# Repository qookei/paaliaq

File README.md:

# Paaliaq

Paaliaq is a WDC W65C816-based single board computer and the
accompanying software, with support for e.g. modern memory management
features, and kernel/user priviledge separation.

The project is currently in early stages of development, with most of
the current work focusing on the chipset implemntation. Proper
documentation TBD.

## Specifications

Using the QMTECH XC7A100T Wukong board with the following
specifications as the base FPGA board:

 - Xilinx Artix-7 100T FPGA
 - 32MiB of SDR SDRAM
 - 8MiB SPI flash (holding the bitstream, with free space after it)
 - SD card slot
 - Ethernet port with GMII PHY
 - Some LEDs and buttons
 - 4 PMODs, 40 pin header exposing 34 FPGA I/Os (see below for usage).

Attached to the FPGA board's 40 pin header is an adapter board holding
a DIP40 variant of the 65C816 CPU, currently running at approximately
4 MHz.

## How?

Supporting the features mentioned above is made possible due to the
inclusion of the `ABORTB` signal on the 65C816 CPU, which allows the
currently executing instruction to be aborted, preventing register
changes and memory reads/writes, and allowing the instruction to
potentially be retried after returning from the handler.

To facilitate this, the FPGA contains not only the memory controller
and various peripherals, but also a page-based memory management unit,
which performs address translation and permission checks, signaling
errors to the CPU via the aforementioned abort signal.

## Directory structure and building

Each of the following subdirectories has instructions on how to build
it's contents:

 - `rtl` - The source code for the FPGA implementation of the chipset.
 - `toolchain` - The source code for the toolchain (assembler, etc).
 - `fw` - The source code for the firmware (embedded in BRAM).
 - `kern` - The source code for the kernel (loaded over serial).

## License

This project is licensed under the GNU General Public License, either
version 3, or (at your opinion) any later version.

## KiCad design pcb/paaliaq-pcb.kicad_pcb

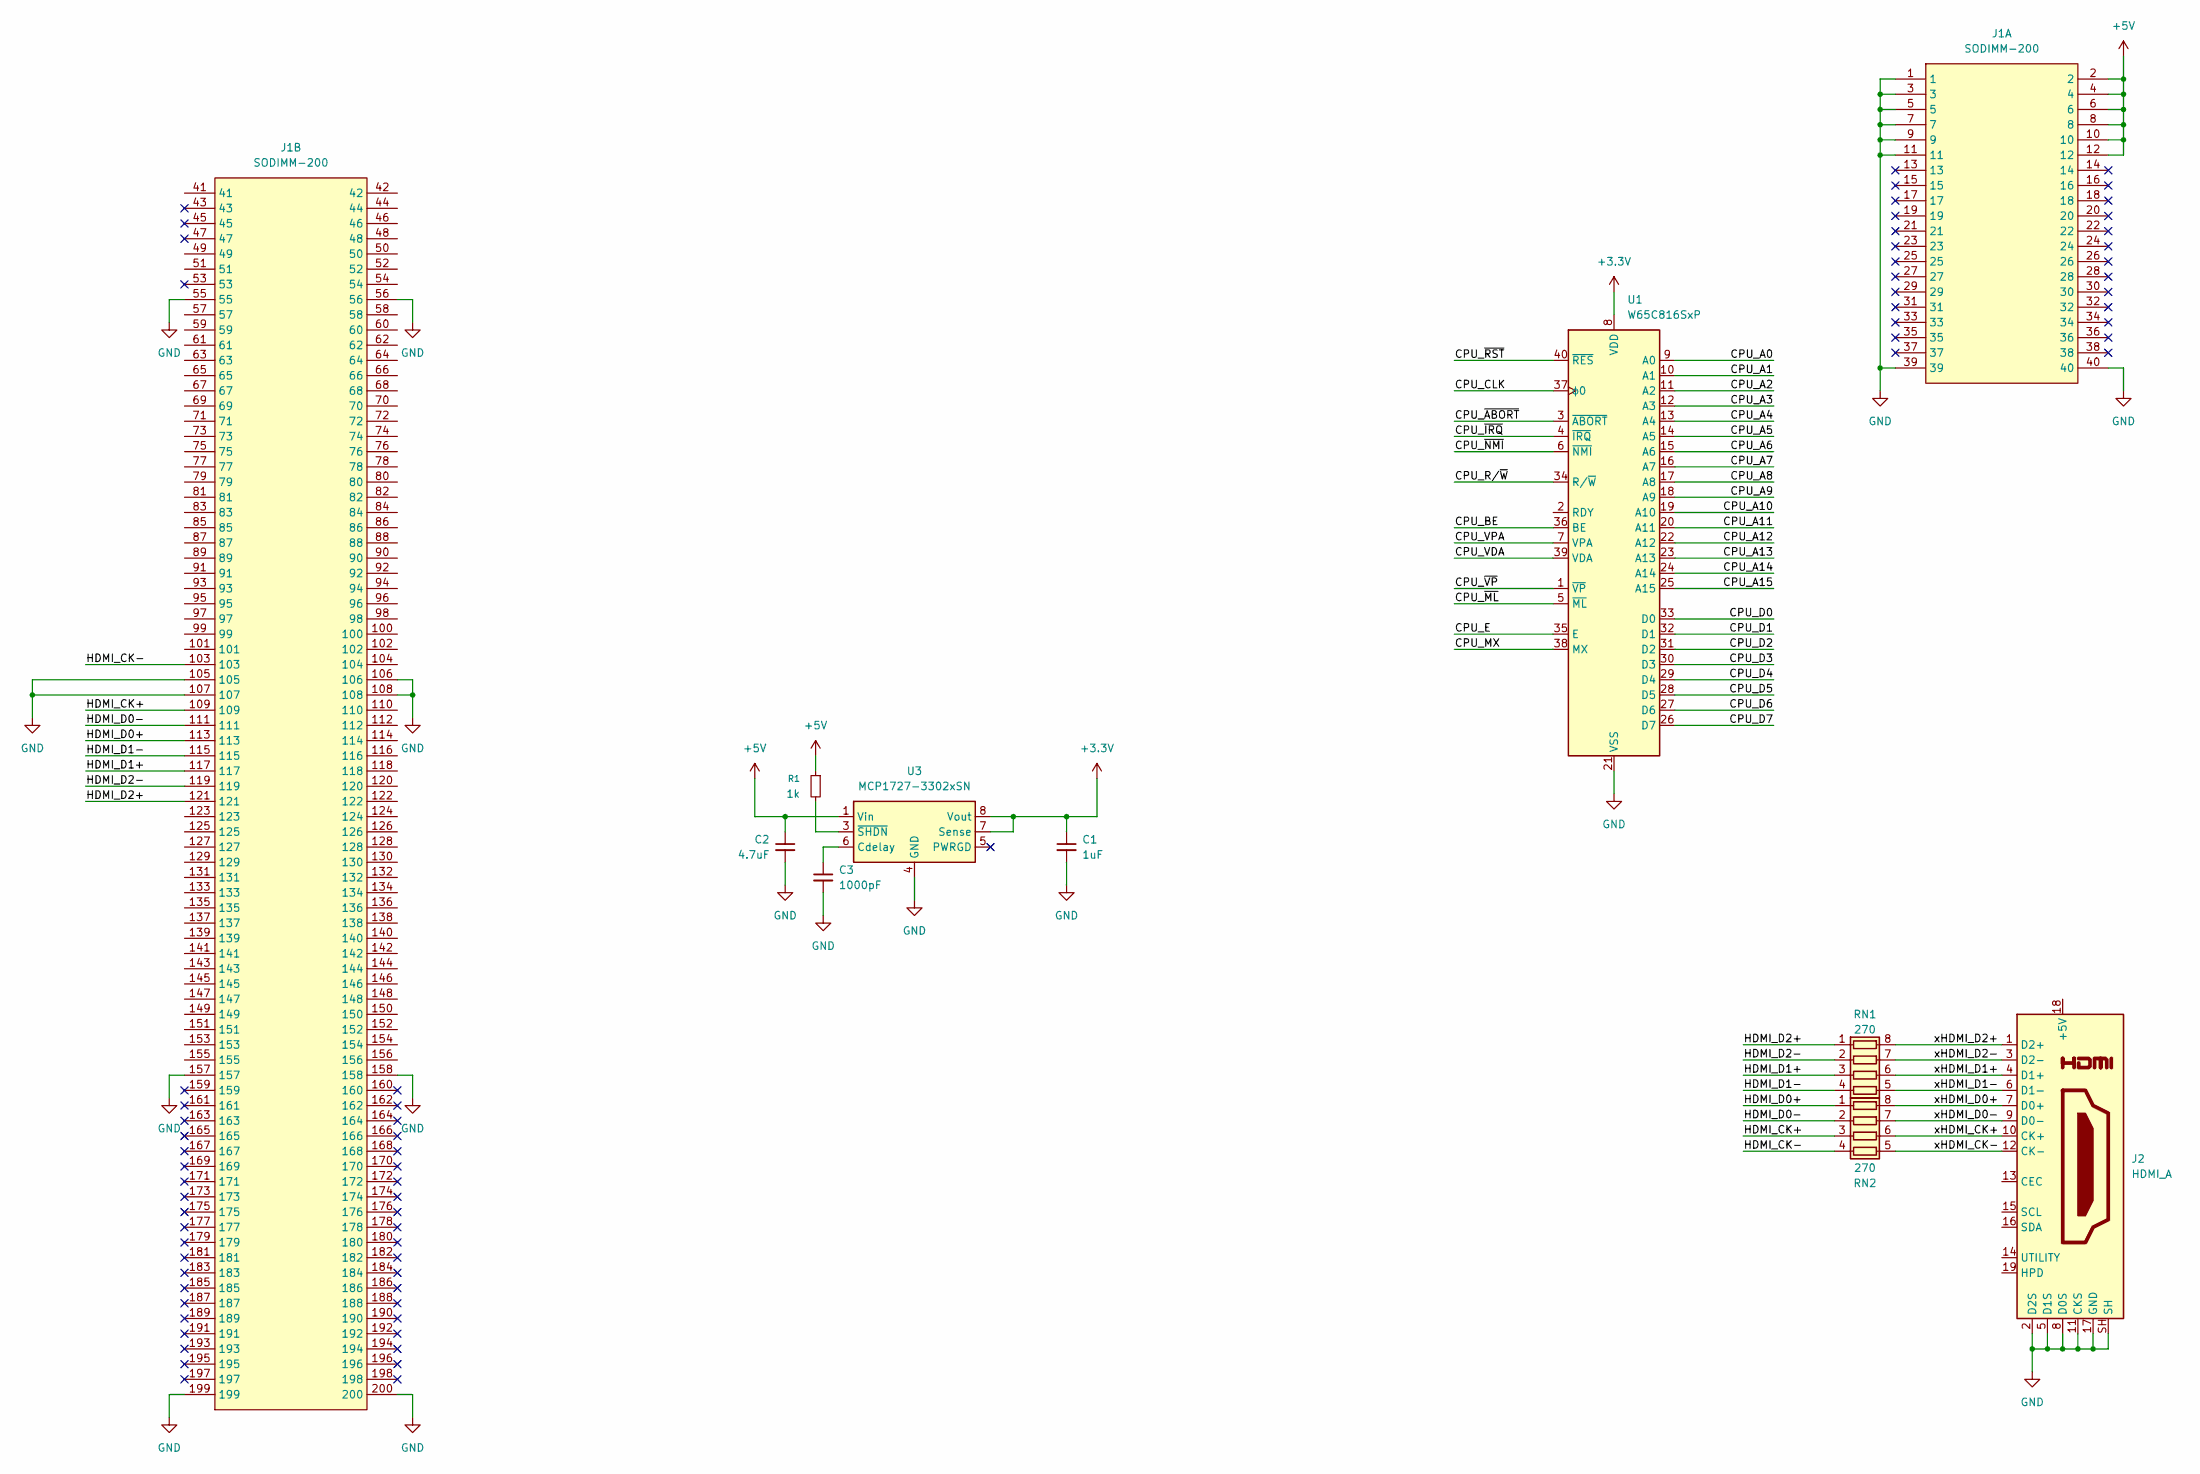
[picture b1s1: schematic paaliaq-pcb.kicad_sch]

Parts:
C1: 1uF; C_0805_2012Metric_Pad1.18x1.45mm_HandSolder
C2: 4.7uF; C_0805_2012Metric_Pad1.18x1.45mm_HandSolder
C3: 1000pF; C_0805_2012Metric_Pad1.18x1.45mm_HandSolder
J1: SODIMM-200; TE_1473005-1_2x100_P0.6mm_Horizontal
J2: HDMI_A; HDMI_A_Amphenol_10029449-x01xLF_Horizontal
R1: 1k; R_0805_2012Metric_Pad1.20x1.40mm_HandSolder
RN1, RN2: 270; R_Array_Convex_4x1206
U1: W65C816SxP; DIP-40_W15.24mm_Socket
U3: MCP1727-3302xSN; SOIC-8_3.9x4.9mm_P1.27mm

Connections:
+3.3V: C1.1, U1.8 (VDD), U3.7 (Sense), U3.8 (Vout)
+5V: C2.1, J1.2, J1.4, J1.6, J1.8, J1.10, J1.12, R1.1, U3.1 (Vin), U3.2 (Vin)
/CPU_A0: U1.9 (A0)
/CPU_A1: U1.10 (A1)
/CPU_A2: U1.11 (A2)
/CPU_A3: U1.12 (A3)
/CPU_A4: U1.13 (A4)
/CPU_A5: U1.14 (A5)
/CPU_A6: U1.15 (A6)
/CPU_A7: U1.16 (A7)
/CPU_A8: U1.17 (A8)
/CPU_A9: U1.18 (A9)
/CPU_A10: U1.19 (A10)
/CPU_A11: U1.20 (A11)
/CPU_A12: U1.22 (A12)
/CPU_A13: U1.23 (A13)
/CPU_A14: U1.24 (A14)
/CPU_A15: U1.25 (A15)
/CPU_BE: U1.36 (BE)
/CPU_CLK: U1.37 (ϕ0)
/CPU_D0: U1.33 (D0)
/CPU_D1: U1.32 (D1)
/CPU_D2: U1.31 (D2)
/CPU_D3: U1.30 (D3)
/CPU_D4: U1.29 (D4)
/CPU_D5: U1.28 (D5)
/CPU_D6: U1.27 (D6)
/CPU_D7: U1.26 (D7)
/CPU_E: U1.35 (E)
/CPU_MX: U1.38 (MX)
/CPU_R/~W: U1.34 (R/~W)
/CPU_VDA: U1.39 (VDA)
/CPU_VPA: U1.7 (VPA)
/CPU_~ABORT: U1.3 (~ABORT)
/CPU_~IRQ: U1.4 (~IRQ)
/CPU_~ML: U1.5 (~ML)
/CPU_~NMI: U1.6 (~NMI)
/CPU_~RST: U1.40 (~RES)
/CPU_~VP: U1.1 (~VP)
/HDMI_CK+: J1.109, RN2.3 (R3.1)
/HDMI_CK-: J1.103, RN2.4 (R4.1)
/HDMI_D0+: J1.113, RN2.1 (R1.1)
/HDMI_D0-: J1.111, RN2.2 (R2.1)
/HDMI_D1+: J1.117, RN1.3 (R3.1)
/HDMI_D1-: J1.115, RN1.4 (R4.1)
/HDMI_D2+: J1.121, RN1.1 (R1.1)
/HDMI_D2-: J1.119, RN1.2 (R2.1)
/xHDMI_CK+: J2.10 (CK+), RN2.6 (R3.2)
/xHDMI_CK-: J2.12 (CK-), RN2.5 (R4.2)
/xHDMI_D0+: J2.7 (D0+), RN2.8 (R1.2)
/xHDMI_D0-: J2.9 (D0-), RN2.7 (R2.2)
/xHDMI_D1+: J2.4 (D1+), RN1.6 (R3.2)
/xHDMI_D1-: J2.6 (D1-), RN1.5 (R4.2)
/xHDMI_D2+: J2.1 (D2+), RN1.8 (R1.2)
/xHDMI_D2-: J2.3 (D2-), RN1.7 (R2.2)
GND: C1.2, C2.2, C3.2, J1.1, J1.3, J1.5, J1.7, J1.9, J1.11, J1.39, J1.40, J1.55, J1.56, J1.105, J1.106, J1.107, J1.108, J1.157, J1.158, J1.199, J1.200, J2.2 (D2S), J2.5 (D1S), J2.8 (D0S), J2.11 (CKS), J2.17 (GND), J2.SH, U1.21 (VSS), U3.4 (GND)
unnamed: C3.1, U3.6 (Cdelay)
unnamed: R1.2, U3.3 (~SHDN)

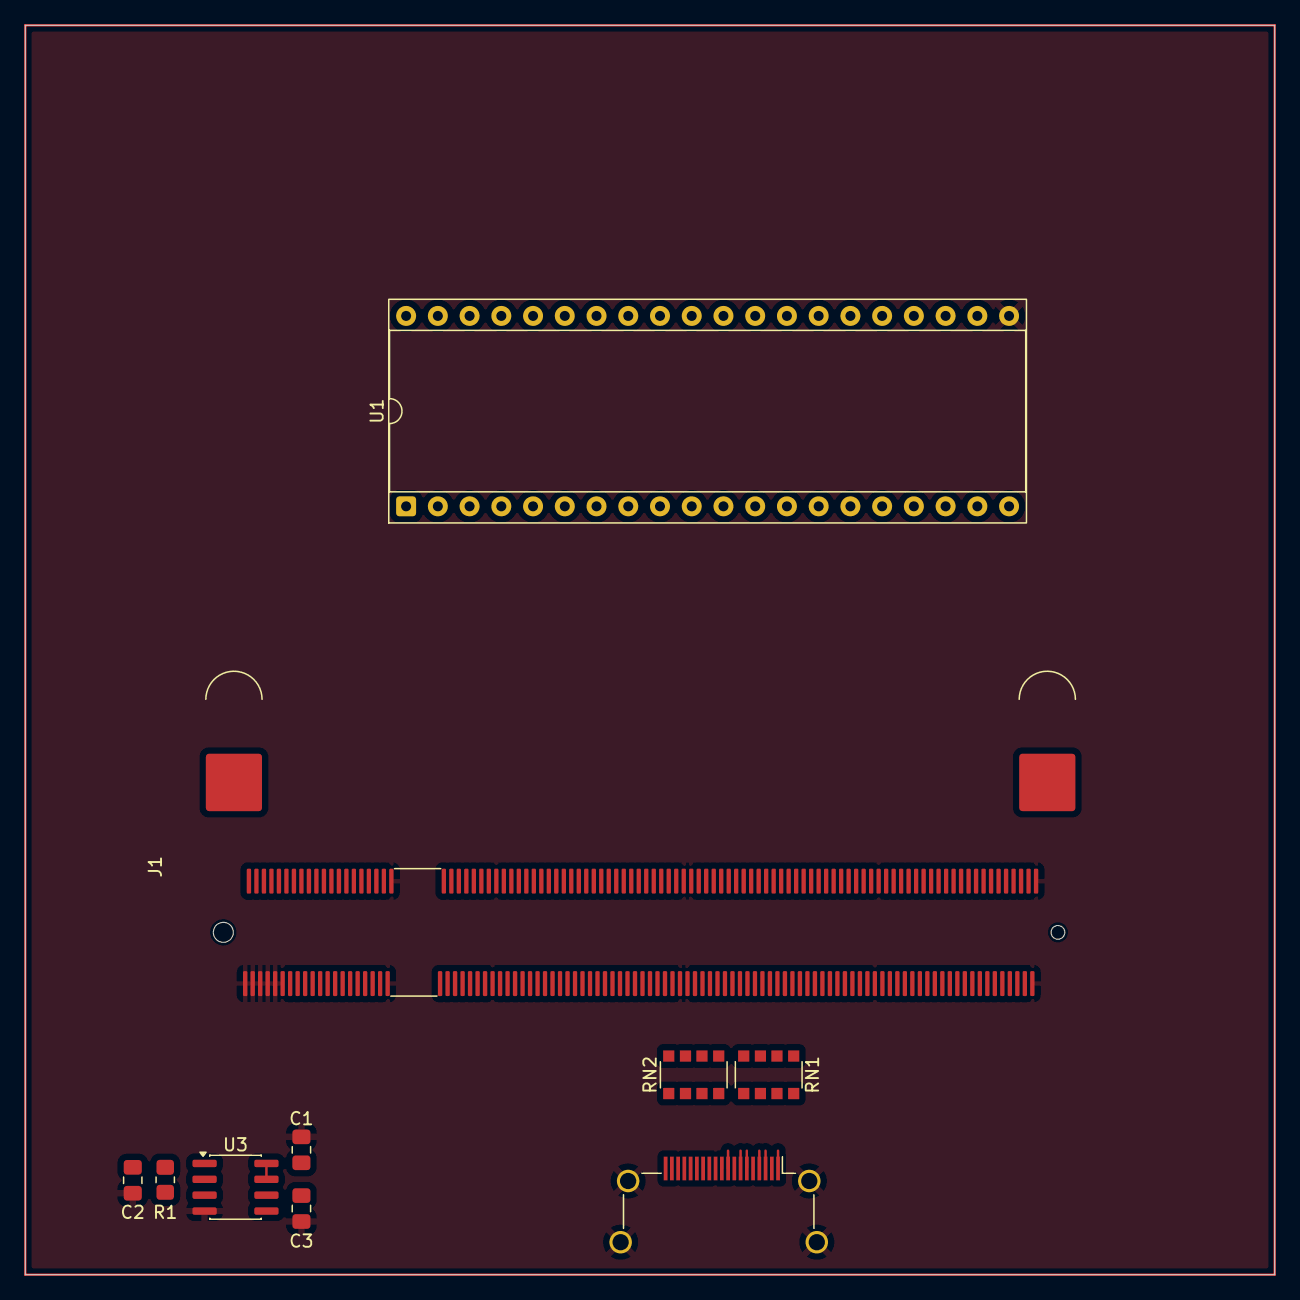
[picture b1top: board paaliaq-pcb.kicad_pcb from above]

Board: 2 copper layers, 100.0 x 100.0 mm, 10 parts (0 on the bottom side), 21 nets.

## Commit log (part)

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2023-03-10 Import RTL code
2023-03-11 rtl: Add GPLv3+ header to build system files
2023-03-20 meta: Add README for the toolchain, and mention in root README
2023-03-22 rtl: MMU: Trigger TLB write on write to way index register
2023-03-23 toolchain: as: Replace custom partial-apply with SRFI 26 cut
2023-06-20 toolchain: Reformat code
2023-10-28 rtl-new: Begin work on the RTL rewrite using Amaranth
    Other changes include finally using Wishbone instead of what I cobbled
    together.
    MMU, external RAM interface, etc TBD.
2023-10-31 rtl-new: Add external RAM interface
2024-02-27 toolchain: Rewrite assembler
    This is still not hooked up to anything, and I still plan on changing
    the symbols for the various addressing modes.
2024-02-27 toolchain: Add module with code to emit ELF files
    Currently only has code to emit object files.
    I think the section procedures (%.text, etc.) ought to be in their own
    module, I think the assembler will use them as well.
    The string interning procedure also seems useful, and should probably
    go into some generic utility module.
2024-02-27 toolchain: Use the new modules in asm2.scm
2024-02-28 toolchain: Add module with helpers for creating sections
2024-02-29 toolchain: Add helper assemble procedure
    This procedure wraps around assemble-many, automatically creating a
    default state, and discarding the resulting output state.
2024-03-01 toolchain: Fix opcode for COP instruction
2024-03-01 toolchain: Add top-level assembler program script
2024-03-01 toolchain: Add -l/--load-path flag to assembler
2024-03-01 toolchain: Support sub-lists of instructions in assembler DSL
    This allows for regular unquote to be used instead of
    unquote-splicing, reducing the visual noise a bit (,x vs ,@x).
2024-03-16 toolchain: Add address field to elf-scn
2024-03-24 toolchain: Allow for specifying type and entry of emitted ELFs
2024-05-18 toolchain: Fix phe addressing modes
    Fix support for (phe rel), and turn (phe ind-dp) into (phe dp).
2025-01-30 rtl-new: Begin refactoring and porting to an ECP5 platform
    Port to amaranth.lib.wiring for nice helpers for wiring stuff up, add
    support for using a 65C816 soft-core for now (until I actually buy a
    real chip and hook it up), add an UART transmitter, and make the code
    synthesize on an Lattice ECP5 board (Colorlight 5A-75B V8.2).
2025-01-31 rtl-new: Rework how the CPU Wishbone bridge state machine works
    Each state that uses the counter has the counter start at 0, instead
    of the counter counting up from the point the clock went low.
2025-01-31 rtl-new: Add separate states for managing CPU reset
2025-02-04 rtl-new: Move CPU debug probe into separate component
2025-02-04 rtl-new: Add an UART peripheral
2025-02-05 rtl-new: Reorganize UART status register
    This allows the BIT instruction to be used to quickly check the flags.
2025-02-06 rtl-new: Add an interrupt controller and wire up timer
2025-02-09 rtl-new: Clear UART RX clock enable when going idle
2025-02-10 rtl-new: Implement a simple MMU
2025-02-10 rtl-new: Display abort signal state in bus trace
2025-02-17 rtl-new: Add a simple SDRAM controller and wire it up
    The controller as it stands is pretty unoptimized, and wastes 3/4ths
    of the 8MiB of SDRAM on-board.
    Some optimizations include: keeping rows active between accesses,
    adding a cache and doing larger bursts for reads and writes (which
    would also help solve the wasted space problem).
    The RAM is partially wasted because the board I'm using has DQM{0..3}
2025-02-17 rtl-new: Let wait-high timeout run while a transfer is in progress
    For slower bus transactions (e.g. ones to SDRAM) staying in the
    wait-high state for a constant amount of time meant the cycle ended up
    being longer than needed, lowering the average CPU clock speed. Since
    the complete-transaction state also holds the clock high, nothing
    stops us from starting counting the remaining cycles from that point
    instead.
2025-02-19 toolchain: Remove obsolete and unused code
    These files are completely unused and have been superseded by the new
    toolchain.
2025-02-19 rtl-new: Factor out SDRAM platform connection to own component
2025-02-19 rtl-new: Refactor TopLevel to instantiate components in elaborate
2025-02-19 rtl-new: Replace handwritten UART PHY with one from amaranth-stdio
    Also add missing FFSynchronizer on the RX pin (AFAICT with this
    missing, the reciever sometimes gets stuck at 75MHz).
2025-02-19 meta: Add .gitignore
2025-02-19 boot: Add a serial bootloader and make memory tester loadable
2025-02-22 rtl: Use separate counters for CPU FSM delays
    This improves the max frequency a bit (by improving the on-chip layout
    I assume).
2025-05-10 rtl: Accept command-line configuration parameters for the SoC
2025-05-11 rtl: Remove obsolete FPGA top-level file
2025-05-11 rtl: Add default value for target frequncy parameter
2025-05-12 meta: Reword README.md
    Update the specifications, and reword the intro and "How?" sections.
2025-05-17 rtl: Split read/write paths in CPU bridge
2025-05-18 rtl: Replace >= with == in CPU interface logic
    Not sure if this makes a huge difference, but the change makes sense
    in my head. :^)
2025-05-18 scripts: Add scripts for remote debugging with OpenOCD
2025-05-23 scripts: Add script to program the FPGA via OpenOCD
    Instead of having to kill OpenOCD, program the FPGA using ecpprog,
    then restarting OpenOCD, I can now just keep OpenOCD open permanently.
2025-05-24 scripts: Add tcl procedures for CPU tracing
2025-06-26 toolchain: Add skeleton for linker entry point
2025-06-26 toolchain: Add relocation-related linker module
2025-06-26 toolchain: Parse base address as hex by default
    Make does not escape the `#` within strings when setting
    target-specific variables, so let's just parse this as hex so the user
    doesn't need to specify the `#x` prefix (this will later be handled by
    the linker script anyway).
2025-06-27 toolchain: Add DSL macro for defining null-terminated strings
2025-06-27 build, boot: Rework build system and merge memtest into boot0
    Rework the build system in anticipation of many separate programs
    existing in the same source tree.
    The memory test program is small enough that this doesn't hurt to do,
    and it avoids needing to load it over serial.
2025-07-10 rtl: Generate P65C816 soft-core via Makefile
2025-07-10 rtl: Generalize ECP5 PLL instatiation code
2025-07-11 rtl: Fix Makefile rule dependencies
    If using the existing copy of P65C816.v, we don't want to clone the
    repo if it's missing (which would then trigger a rebuild of the
    Verilog file).
2025-07-15 rtl: Begin working on HDMI video output
    So far I have 1080p output working with a test pattern.
2025-07-15 build: Fix dependency between FPGA bitstream and boot ROM
2025-07-15 fw: Dump area around failing address in memory test
2025-07-20 rtl: Add a 128x48 color text framebuffer
    This provides an interface similar to VGA text mode, with two bytes
    per character: one for the CP 437 code, and one for the foreground and
    background colors. Also implements a text cursor (although it's not
    yet wired up to registers to move it around).
2025-07-20 fw: Print to both the UART and screen
2025-11-16 rtl: Don't use differencial pair I/Os for HDMI
    This is needed for the iCESugar-pro w/ dev-board, which has HDMI
    routed to pins that don't form differencial pairs...
2025-11-16 fw: Fix detection of when to scroll text screen
2025-11-16 fw: Synchronize hardware cursor with software position
2025-11-16 rtl: Use a nicer color scheme for the text video output
2025-11-30 rtl: Add proper CDC for cursor register writes
    Turns out reading the timing reports is useful...
2025-11-30 rtl: Fix PLL phase parameter computation
    Now any arbitrary phase is supported, and the parameters should match
    what's produced by vendor tools.
2025-11-30 wip dvi phy
2025-12-01 rtl: Insert combinatorial cuts in some bus subordinates
    This helps improve timing in the SoC clock domain. The CSR bus bridge
    had a lot of extra delay coming out of the bus, and the internal ram
    has a large clk-to-q delay on the BRAM data output, which in
    combination with the logic and routing delays went over 10 ns.
    The current critical path is inside the MMU, which will be more
    problematic to solve.
2025-12-19 rtl: Use DDR buffer instead of PLL for 180deg phase shift
2025-12-21 rtl: Align peripheral CSR base address to 256 bytes
    This means that changing the CSRs in one peripheral wont move around
    other CSRs as long as it doesn't grow beyond 256 bytes.
2025-12-21 fw: Make memory test faster by using 16-bit accesses
2025-12-21 scripts: Update CSR addresses in JTAG debug script
2025-12-23 rtl: Add an initial SPI controller implementation
    TODOs:
    - clock divisor
    - more sophisticated transaction interface
    - 1x/2x/4x width support
    - deeper FIFOs
2025-12-26 rtl: Add 2x and 4x transfer width support
2025-12-28 rtl: Update SPI output enables before every clock cycle
    Without this, if the first segment is TX, we fail to properly
    configure the output enables for it.
2025-12-28 rtl: Add user permission bit to page table entries
2025-12-30 fw: Perform ICRNL conversion in UART echo
2026-01-06 build: Revert rule cleanup due to recursive Make uses
    I'm planning on not using recursive Make but haven't gotten around to
    it yet, and the cleanup caused rebuilds to not happen properly.
2026-01-25 fw: Remove old serial boot option
2026-02-09 fw: Fix minor bugs in ZMODEM implementation
    Fix XOFF check (XOFF is DC3 not DC4 in ASCII). Fix missing mask to
    only check the type byte when receiving ZDATA.
2026-04-12 rtl: Use S7MMCM in video output logic
2026-04-12 rtl: Add Artix-7 based top level
    This is targeting the QMTECH XC7A100T WUKONG board (V3).
2026-04-12 rtl: Rework SDRAM controller in preparation of separate clock domain
2026-04-12 rtl: Add clock groups constraint for Artix 7
2026-04-20 meta: Ignore all __pycache__ directories
2026-05-02 rtl: Move everything into a "paaliaq" subdirectory
2026-05-02 rtl: Provide clock information via platform
2026-05-02 rtl: Wire up SPI controller for on-board flash on Artix-7
2026-05-04 rtl: Provide SPI pins through platform
2026-05-05 rtl: Fix balance calculations in TMDS encoder
    I'm surprised this worked at all...
2026-05-05 fw: Show off all colors on text video display
2026-05-11 rtl: Add W65C816 IOs for Artix 7 board
    These are the IOs when using the recently-made adapter board.
2026-05-11 rtl: Slow down CPU timings to ~1MHz
    This is temporary...
2026-05-14 toolchain: Add helpers for switching register sizes
    These helpers also include a NOP instruction after the REP/SEP to deal
    with older W65C816 CPUs not fully executing them within the two cycles.
2026-05-14 rtl: Improve CPU abort handling
    We now maintain the strict timings for the ABORT signal (assert before
    rising clock edge, deassert right after rising clock edge).
    Additionally, we cause the instruction to be a no-op for the entire
    remaining duration if a cycle is aborted.
2026-05-14 rtl: Only raise ABORT on first aborted cycle
2026-05-14 kern: Use register size switching helpers
2026-05-18 rtl: Wire up UART debug bridge
2026-05-23 scripts: Add script to run processor tests over debug interface
    The goal of this is to validate the tests in the SingleStepTests/65816
    repository against real hardware.
2026-05-24 scripts: Print test results
2026-05-27 scripts: Expand test runner script
